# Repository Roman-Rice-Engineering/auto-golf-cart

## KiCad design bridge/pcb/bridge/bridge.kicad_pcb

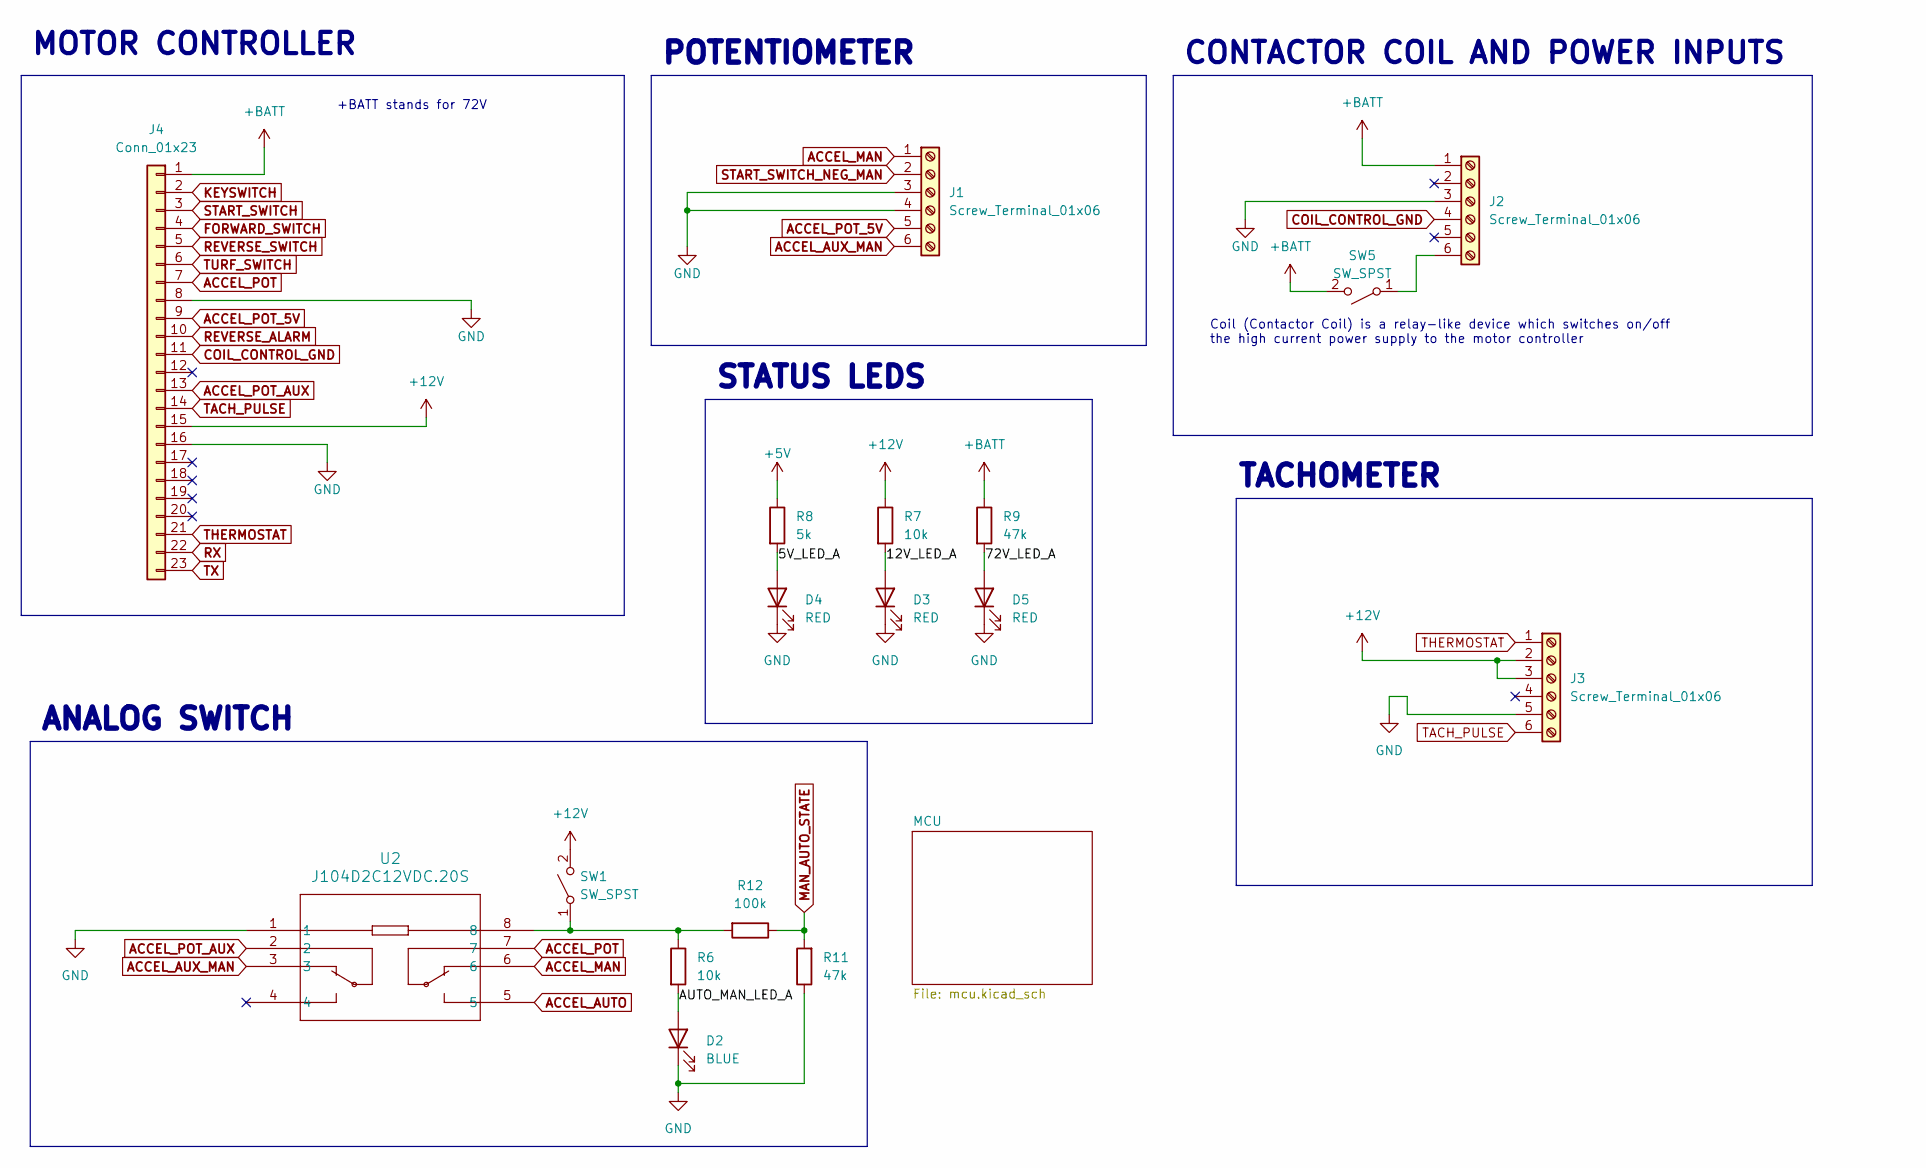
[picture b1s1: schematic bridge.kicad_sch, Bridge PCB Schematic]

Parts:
D2: BLUE; LED_D5.0mm
D3, D4, D5: RED; LED_D5.0mm
J1, J2, J3: Screw_Terminal_01x06; TE_2-1437667-9
J4: Conn_01x23; TE_AMPSEAL_1-776087-x_3Rows_23_P0.4mm_Horizontal
R6, R7: 10k; THT_RESISTOR_WITH_VALUE
R8: 5k; THT_RESISTOR_WITH_VALUE
R9, R11: 47k; THT_RESISTOR_WITH_VALUE
R12: 100k; THT_RESISTOR_WITH_VALUE
SW1, SW5: SW_SPST; PinHeader_1x02_P2.54mm_Vertical
U2: J104D2C12VDC.20S; RELAY8_J104D2C12VDC.20S_CRS

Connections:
+5V: R8.1; also elsewhere on the board
+12V: J3.2, J3.3, J4.15, R7.1, SW1.2 (B); also elsewhere on the board
+BATT: J2.1, J2.6, J4.1, R9.1, SW5.1 (A), SW5.2 (B); also elsewhere on the board
/5V_LED_A: D4.2 (A), R8.2
/12V_LED_A: D3.2 (A), R7.2
/72V_LED_A: D5.2 (A), R9.2
/AUTO_MAN_LED_A: D2.2 (A), R6.2
ACCEL_AUTO: U2.5; also elsewhere on the board
ACCEL_AUX_MAN: J1.6, U2.3; also elsewhere on the board
ACCEL_MAN: J1.1, U2.6
ACCEL_POT: J4.7, U2.7
ACCEL_POT_5V: J1.5, J4.9
ACCEL_POT_AUX: J4.13, U2.2; also elsewhere on the board
COIL_CONTROL_GND: J2.4, J4.11
FORWARD_SWITCH: J4.4; also elsewhere on the board
GND: D2.1 (K), D3.1 (K), D4.1 (K), D5.1 (K), J1.3, J1.4, J2.3, J3.5, J4.8, J4.16, R11.1, U2.1; also elsewhere on the board
KEYSWITCH: J4.2; also elsewhere on the board
MAN_AUTO_STATE: R11.2, R12.1; also elsewhere on the board
unnamed: R6.1, R12.2, SW1.1 (A), U2.8
REVERSE_ALARM: J4.10
REVERSE_SWITCH: J4.5; also elsewhere on the board
RX: J4.22
START_SWITCH: J4.3; also elsewhere on the board
START_SWITCH_NEG_MAN: J1.2; also elsewhere on the board
TACH_PULSE: J3.6, J4.14
THERMOSTAT: J3.1, J4.21
TURF_SWITCH: J4.6; also elsewhere on the board
TX: J4.23

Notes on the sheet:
STATUS LEDS
MOTOR CONTROLLER
Coil (Contactor Coil) is a relay-like device which switches on/off the high current power supply to the motor controller
POTENTIOMETER
+BATT stands for 72V
TACHOMETER
CONTACTOR COIL AND POWER INPUTS
ANALOG SWITCH

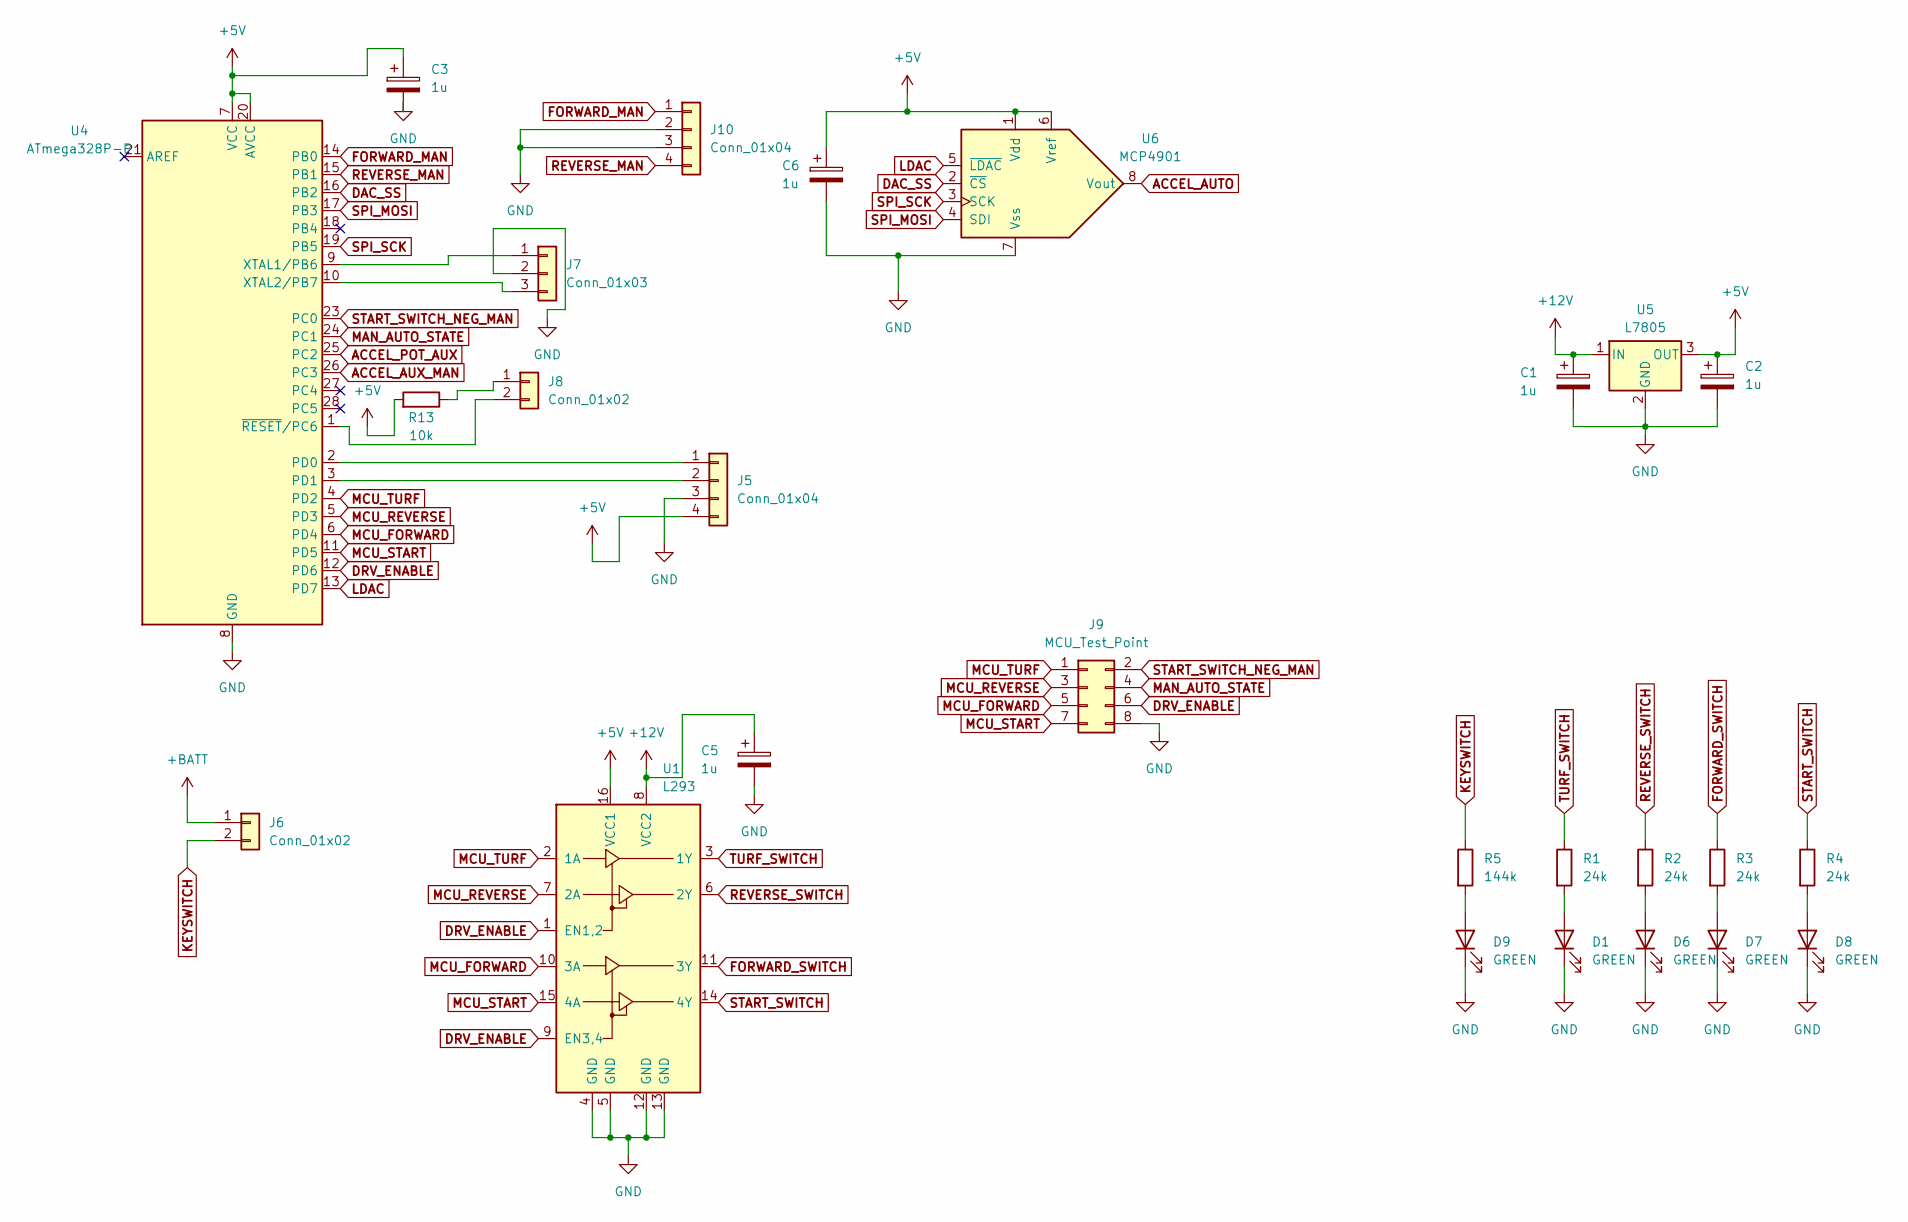
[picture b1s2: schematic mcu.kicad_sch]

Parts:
C1, C2, C3, C5, C6: 1u; CP_Radial_D5.0mm_P2.00mm
D1, D6, D7, D8, D9: GREEN; LED_D5.0mm
J5: Conn_01x04; PinHeader_1x04_P2.54mm_Vertical
J6, J8: Conn_01x02; PinHeader_1x02_P2.54mm_Vertical
J7: Conn_01x03; PinHeader_1x03_P2.54mm_Vertical
J9: MCU_Test_Point; PinHeader_2x04_P2.54mm_Vertical
J10: Conn_01x04
R1, R2, R3, R4: 24k; THT_RESISTOR_WITH_VALUE
R5: 144k; THT_RESISTOR_WITH_VALUE
R13: 10k; THT_RESISTOR_WITH_VALUE
U1: L293; DIP-16_W7.62mm
U4: ATmega328P-P; DIP-28_W7.62mm
U5: L7805; TO-220-3_Horizontal_TabDown
U6: MCP4901

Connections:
+5V: C2.1, C3.1, C6.1, J5.4, R13.2, U1.16 (VCC1), U4.7 (VCC), U4.20 (AVCC), U5.3 (OUT), U6.1 (Vdd), U6.6 (Vref); also elsewhere on the board
+12V: C1.1, C5.1, U1.8 (VCC2), U5.1 (IN); also elsewhere on the board
+BATT: J6.1; also elsewhere on the board
ACCEL_AUTO: U6.8 (Vout); also elsewhere on the board
ACCEL_AUX_MAN: U4.26 (PC3); also elsewhere on the board
ACCEL_POT_AUX: U4.25 (PC2); also elsewhere on the board
DAC_SS: U4.16 (PB2), U6.2 (~CS)
DRV_ENABLE: J9.6, U1.1 (EN1,2), U1.9 (EN3,4), U4.12 (PD6)
FORWARD_MAN: J10.1, U4.14 (PB0); also elsewhere on the board
FORWARD_SWITCH: R3.1, U1.11 (3Y); also elsewhere on the board
GND: C1.2, C2.2, C3.2, C5.2, C6.2, D1.1 (K), D6.1 (K), D7.1 (K), D8.1 (K), D9.1 (K), J5.3, J7.2, J9.8, J10.2, J10.3, U1.4 (GND), U1.5 (GND), U1.12 (GND), U1.13 (GND), U4.8 (GND), U4.22 (GND), U5.2 (GND), U6.7 (Vss); also elsewhere on the board
KEYSWITCH: J6.2, R5.1; also elsewhere on the board
LDAC: U4.13 (PD7), U6.5 (~LDAC)
MAN_AUTO_STATE: J9.4, U4.24 (PC1); also elsewhere on the board
MCU_FORWARD: J9.5, U1.10 (3A), U4.6 (PD4)
MCU_REVERSE: J9.3, U1.7 (2A), U4.5 (PD3)
MCU_START: J9.7, U1.15 (4A), U4.11 (PD5)
MCU_TURF: J9.1, U1.2 (1A), U4.4 (PD2)
unnamed: D1.2 (A), R1.2
unnamed: D6.2 (A), R2.2
unnamed: D7.2 (A), R3.2
unnamed: D8.2 (A), R4.2
unnamed: D9.2 (A), R5.2
unnamed: J5.1, U4.2 (PD0)
unnamed: J5.2, U4.3 (PD1)
unnamed: J7.1, U4.9 (XTAL1/PB6)
unnamed: J7.3, U4.10 (XTAL2/PB7)
unnamed: J8.1, R13.1
unnamed: J8.2, U4.1 (~RESET/PC6)
REVERSE_MAN: J10.4, U4.15 (PB1); also elsewhere on the board
REVERSE_SWITCH: R2.1, U1.6 (2Y); also elsewhere on the board
SPI_MOSI: U4.17 (PB3), U6.4 (SDI)
SPI_SCK: U4.19 (PB5), U6.3 (SCK)
START_SWITCH: R4.1, U1.14 (4Y); also elsewhere on the board
START_SWITCH_NEG_MAN: J9.2, U4.23 (PC0); also elsewhere on the board
TURF_MAN: U4.18 (PB4); also elsewhere on the board
TURF_SWITCH: R1.1, U1.3 (1Y); also elsewhere on the board

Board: 2 copper layers, 44 parts (0 on the bottom side), 48 nets, no tracks yet.

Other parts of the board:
SW2, SW3, SW4: SW_SPST; PinHeader_1x02_P2.54mm_Vertical

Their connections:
FORWARD_MAN: SW2.1 (A); also elsewhere on the board
GND: SW2.2 (B), SW3.2 (B), SW4.2 (B); also elsewhere on the board
REVERSE_MAN: SW3.1 (A); also elsewhere on the board
TURF_MAN: SW4.1 (A); also elsewhere on the board

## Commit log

2023-11-08 Set up shematic for bridge pcb
    - Set up the inputs and outputs for the bridge pcb board
    - Labelled which pins connect to what
2023-11-10 Completed schematic I/O connections
2024-02-08 Changed circuit board setup to one board bridge
2024-02-09 Added basic functions to PCB
2024-02-09 Fixed issues, added DAC
2024-02-09 Changed PCB to use correct tht resistor footprint
2024-02-09 Completed schematic
2024-02-09 Completed routing of PCB
2024-02-12 Completed silkscreen
2024-02-12 Changed board size to make ordering cheaper
2024-03-07 Rounded board outline
2024-04-06 Started fixing PCB, reduced footprint and changed MCU
2024-04-08 Completed basic functionality PCB
2024-04-30 Fixed incorrect test point labeling
2024-04-30 Fixed PORTB and PORTD of atmega328p being reversed
    Changed RST pin on uart header to be 5V instead and adjusted labels accordingly
2024-04-30 Seperated 5V for accel pot and main 5V supply
    Added 5V and 12V enable PCB headers
2024-04-30 Added capacitors near important components
2024-04-30 Added status LED's for all of the motor controller switches
2024-04-30 Connected ACCEL_POT_MAN and ACCEL_POT_AUX to analog pins 2 and 3 of atmega328p
2024-04-30 Assigned footprints and layed out board
    Removed 5V and 12V enable headers as they added unneeded complexity
2024-04-30 Added extra capacitor for L293
2024-04-30 Completed autorouter routing
2024-04-30 Added needed silkscreen labels for new design
2024-05-01 Changed PCB back to 2 layer
2024-05-07 Changed DAC to MCP4901
2024-05-07 Added connector for manual mode forward and reverse signals
2024-05-16 Reversed 5V and GND on serial connector symbol
2024-05-16 Fixed schematic for manual forward, reverse, and turf switches
    Seperated forward and reverse
    Added turf
    Changed schematic to use switch symbol instead of connector generic
2024-05-16 Assigned footprints and added new components to PCB
2024-05-16 Added clarification to silkscreen for main power input connections
2024-05-17 Updated resistor values to make LEDs brighter
2024-05-17 Improved connector labeling and added more detail
    Labeled wiper 1 and wiper 2 for accel pedal
    Changed +/- to be before COIL instead of after i.e. "-COIL" instead of "COIL-"
2024-05-17 Adjusted LED colors
2024-05-17 Added switch for contactor coil, adjusted labeling
    Slightly changed labels for the KEY and MAN/AUTO switches
2024-05-17 Added a version marker and credits to PCB
2024-05-17 Routed circuit board
2024-05-17 Improved label for start switch input and output
2024-05-20 Created a blank arduino sketch, created a basic config file
2024-05-20 Clarified comment
2024-05-20 Added a code for setting up and writing to DAC
2024-05-21 Made dac_setup automatically zero the output
2024-05-21 Changed FORWARD_REVERSE_NORMALLY_CLOSED
2024-05-21 Added dac_end function
2024-05-22 Created code for buffered input and parsing
2024-05-22 Fixed include order in stringparser.h
2024-05-22 Added function to zero entire buffer
2024-05-22 Added code for manual control
2024-05-22 Completed an untested version of v0.2 PCB comptible firmware
2024-05-23 Removed main.c and changed files to cpp to make compilation work
2024-05-23 Fixed a bug which caused inverse of configured NC setting to be used
2024-05-23 Renamed automatic.hpp to automatic.h
2024-05-28 Changed config.h to fit v0.3 PCB and removed dac.h implementation
2024-05-28 Added turf switch control code to manual.cpp
2024-05-28 Implemented dac.h for new IC
